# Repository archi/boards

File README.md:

A collection of board layouts, licensed under CC-BY-SA-NC 3.0 (commercial license available on request, see LICENSE file).

I am not an electronics engineer, so take these layouts with a grain of salt.

# opa1622-breakout/

A simple breakout board to fit VSON10 op amps (like the OPA1622) into a DIP-8 socket.
Pin 1 is rectangular, the others are round.
Please be aware, the OPA1622 has 2 additional pins:

1. GND, which also connects to the board GND plane and which should be connected to a clean GND.
   If you use a virtual GND, I can not say if that's good for you.
   The IC GND pin is routed to the via next to the DIP pin 1.
   
2. The ENable pin is used to turn the IC on/off by switching it to V+.
   It is routed to the via next to DIP pin 5.
   Per default, it is always connected with a bottom line to V+, going from the via to DIP pin 5.
   If you want to control it via an external signal, cut that line and connect the via to your controller.
   
The OPA1622 datasheet suggests adding two decoupling capacitors from V+ and V- to GND. If you want to add them, there are SMD pads for those (0805 in).
  
**This board is not yet tested!** I'll do a fab run once I have more boards for a panel, and publish a note here on how to get any spares (costs will be just those I had, but feel free to tip).

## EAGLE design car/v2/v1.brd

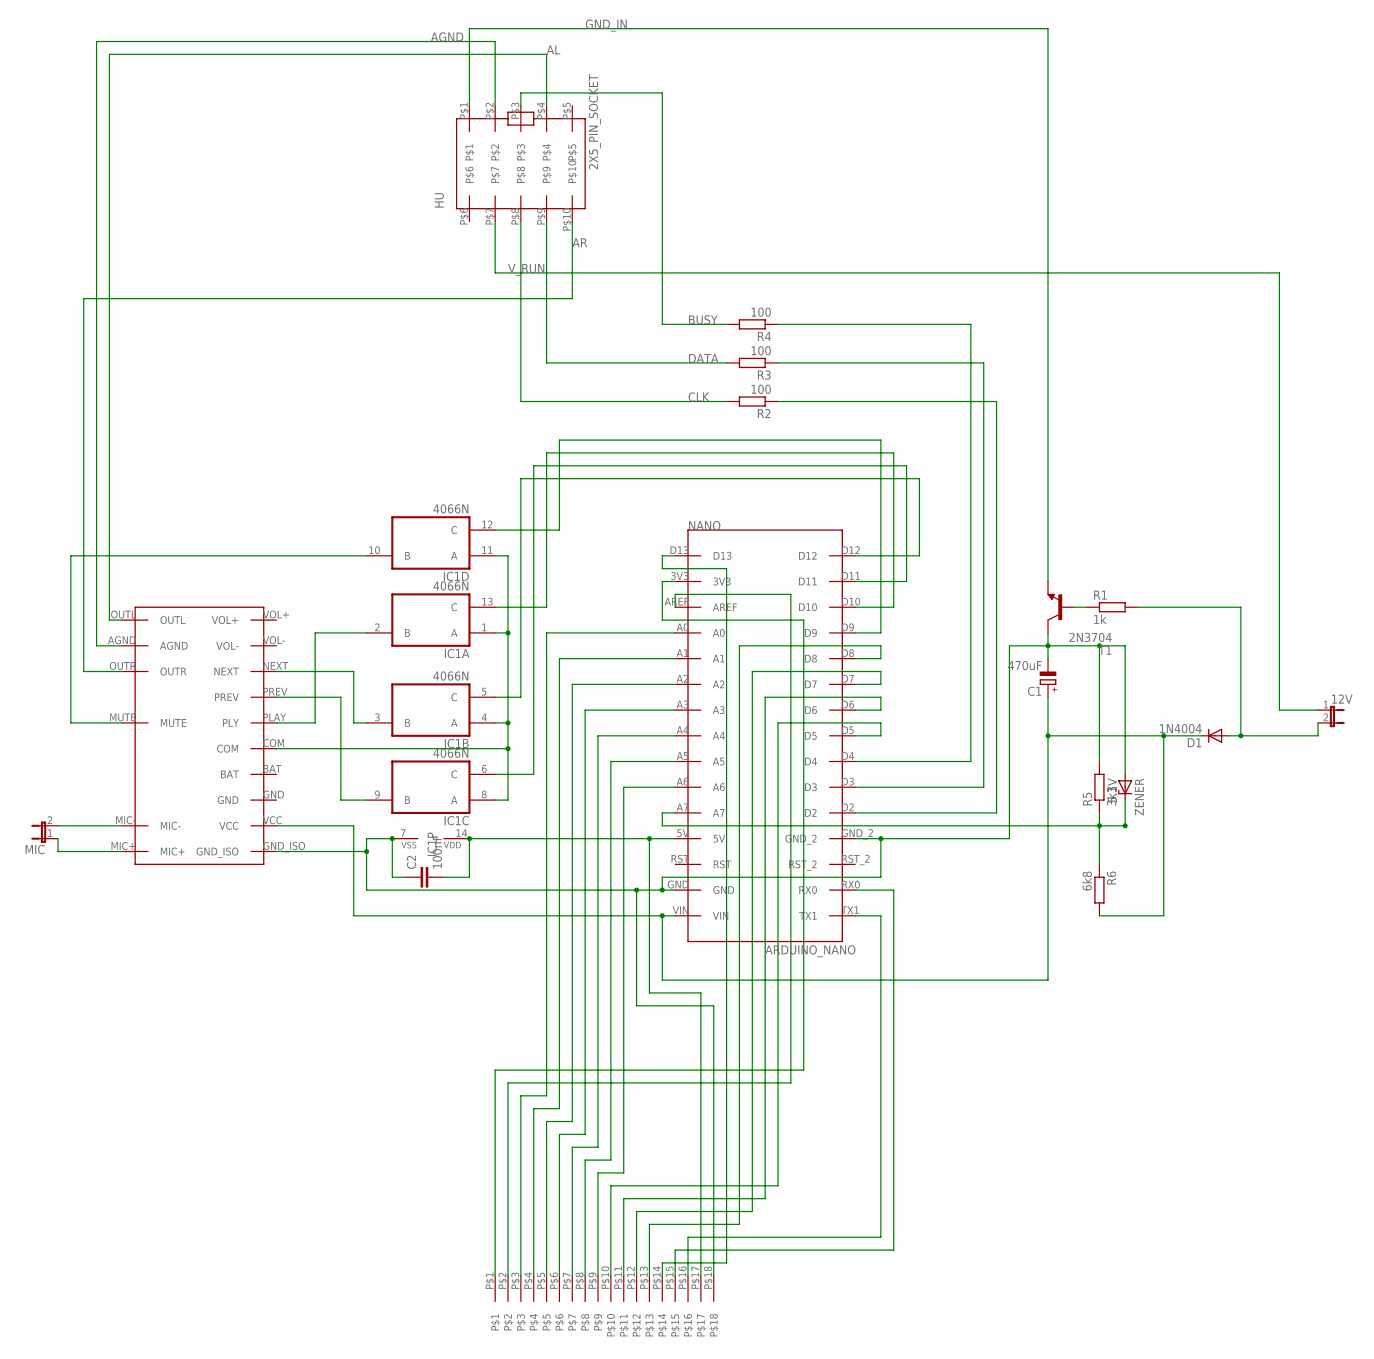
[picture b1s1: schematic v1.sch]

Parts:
12V: JP1E; JP1
C1: 470uF; E3,5-8
C2: 100nF; C1206
D1: 1N4004; DO41-10
HU: 2X5_PIN_SOCKET
IC1: 4066N; DIL14
MIC: JP1E; JP1
NANO: ARDUINO_NANO
R1: 1k; 0207/10
R2, R3, R4: 100; 0207/10
R5: 3k3; 0207/10
R6: 6k8; 0207/10
T1: 2N3704; TO92
U$1: JMP18X1
U$2: CSR8645_MODULE
ZENER: 5.1V; DO41Z10

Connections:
12V: 12V.2, D1.A, R1.2
AGND: HU.P$2, U$2.AGND
AL: HU.P$4, U$2.OUTL
AR: HU.P$10, U$2.OUTR
BUSY: HU.P$3, R4.2
CLK: HU.P$8, R2.2
DATA: HU.P$9, R3.2
GND: C1.-, C2.1, IC1.7 (VSS), NANO.GND, NANO.GND_2, R5.2, T1.2 (C), U$1.P$18, U$2.GND_ISO, ZENER.A
GND_IN: HU.P$1, T1.3 (E)
unnamed: IC1.5 (C), NANO.D12
unnamed: IC1.6 (C), NANO.D11
unnamed: IC1.13 (C), NANO.D10
unnamed: IC1.12 (C), NANO.D9
unnamed: NANO.TX1, U$1.P$16
unnamed: IC1.1 (A), IC1.4 (A), IC1.8 (A), IC1.11 (A), U$2.COM
unnamed: R1.1, T1.1 (B)
unnamed: NANO.A7, R5.1, R6.1, ZENER.C
unnamed: IC1.2 (B), U$2.PLAY (PLY)
unnamed: NANO.RX0, U$1.P$15
unnamed: IC1.9 (B), U$2.PREV
unnamed: IC1.3 (B), U$2.NEXT
unnamed: NANO.D2, R2.1
unnamed: C2.2, IC1.14 (VDD), NANO.5V, U$1.P$17
unnamed: IC1.10 (B), U$2.MUTE
unnamed: NANO.D3, R3.1
unnamed: NANO.D4, R4.1
unnamed: NANO.D13, U$1.P$14
unnamed: NANO.D8, U$1.P$13
unnamed: NANO.D7, U$1.P$12
unnamed: NANO.D6, U$1.P$11
unnamed: NANO.D5, U$1.P$10
unnamed: NANO.A6, U$1.P$9
unnamed: NANO.A5, U$1.P$8
unnamed: NANO.A4, U$1.P$7
unnamed: NANO.A3, U$1.P$6
unnamed: NANO.A2, U$1.P$5
unnamed: NANO.A1, U$1.P$4
unnamed: NANO.A0, U$1.P$3
unnamed: NANO.AREF, U$1.P$2
unnamed: NANO.3V3, U$1.P$1
unnamed: MIC.1, U$2.MIC+
unnamed: MIC.2, U$2.MIC-
VCC: C1.+, D1.C, NANO.VIN, R6.2, U$2.VCC
V_RUN: 12V.1, HU.P$7

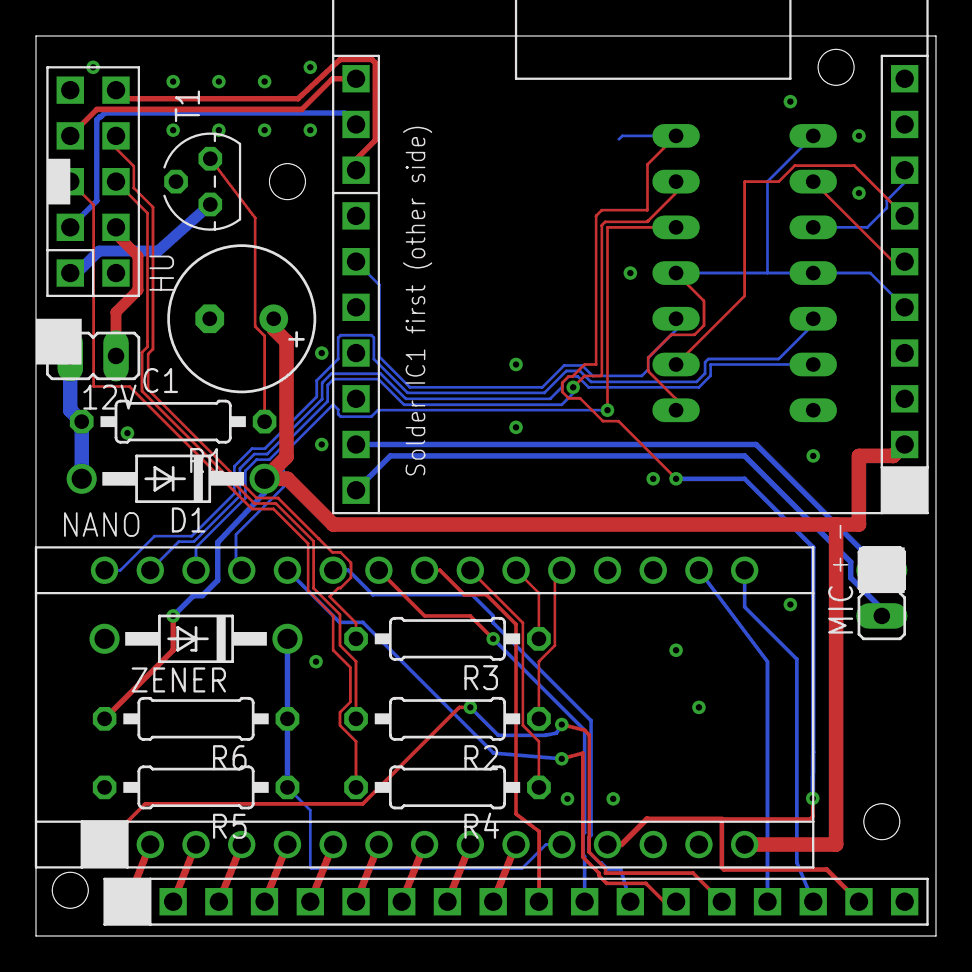
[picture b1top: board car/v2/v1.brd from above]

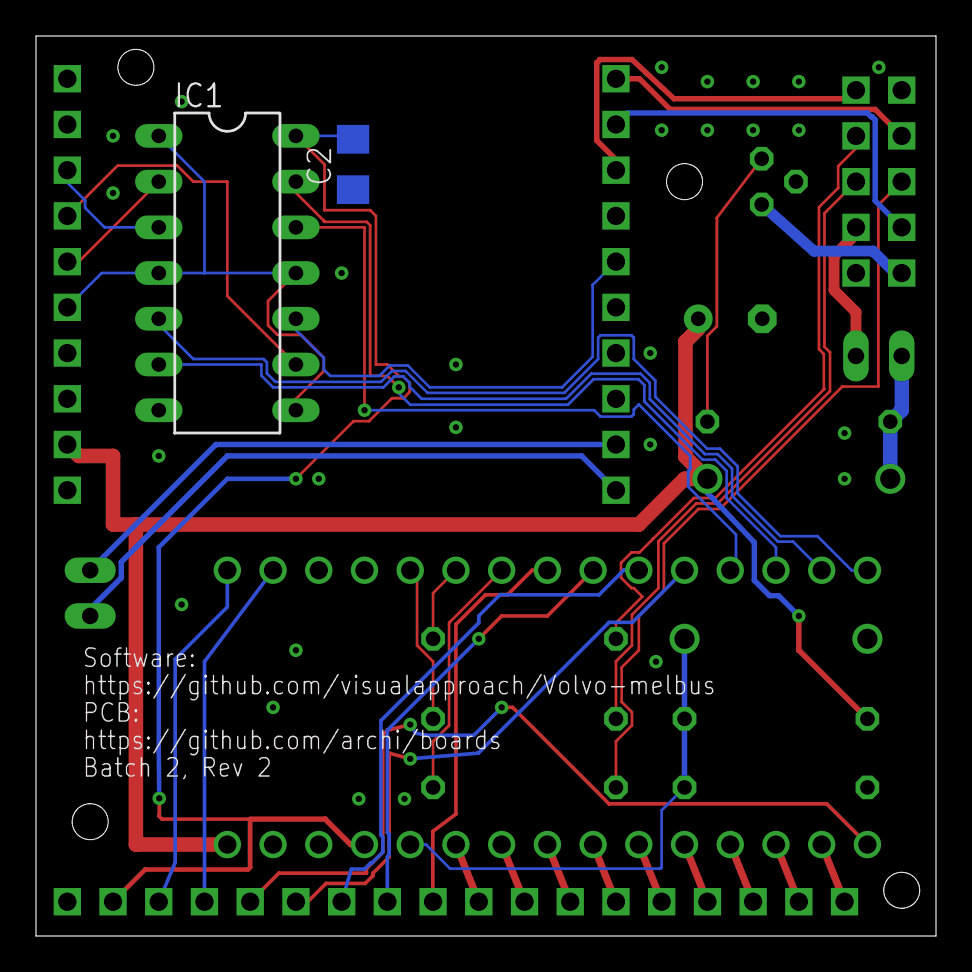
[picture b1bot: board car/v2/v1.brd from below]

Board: 2 copper layers, 50.0 x 50.0 mm, 18 parts (2 on the bottom side), 44 nets.

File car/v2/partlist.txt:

C2		100nF (on bottom!)
IC1		4066N (on bottom!)
C1		470uF
R1		1k
D1 		1N4004
R2,R3,R4	100R
ZENER		5.1V
R6		6k8
R5		3k3
HU		2x5 header
12V		1x2 header
NANO		Arduino Nano (USB port to the PCB edge)
BT		Bluetooth Module CSR8645 with 12V regulator (regulator "on top")

Careful with the 12V header, space is a bit tight to the HU header.

Pin Out HU Header
Numbering is non-default (sorry):
      ___
[1] 2 =3= 4  5
 6  7  8  9 10

PCB		MELBUS
 1 Gnd		Shield
 2 Audio Gnd	2
 3 Busy		5
 4 Audio Left	6
 5 NC		-
 6 NC		-
 7 V_Run (12V)	3 (optional)
 8 Clock	1
 9 Data		4
10 Audio Right	7

The 12V pin header:
The marked pin (outer pin) is connected to the Arduino Nano and the bluetooth module.
The unmarked inner pin is connected to V_Run.

Either connect the outer pin to an external 12V source (e.g. cigarette ligher), or connect the inner to the outer pin.

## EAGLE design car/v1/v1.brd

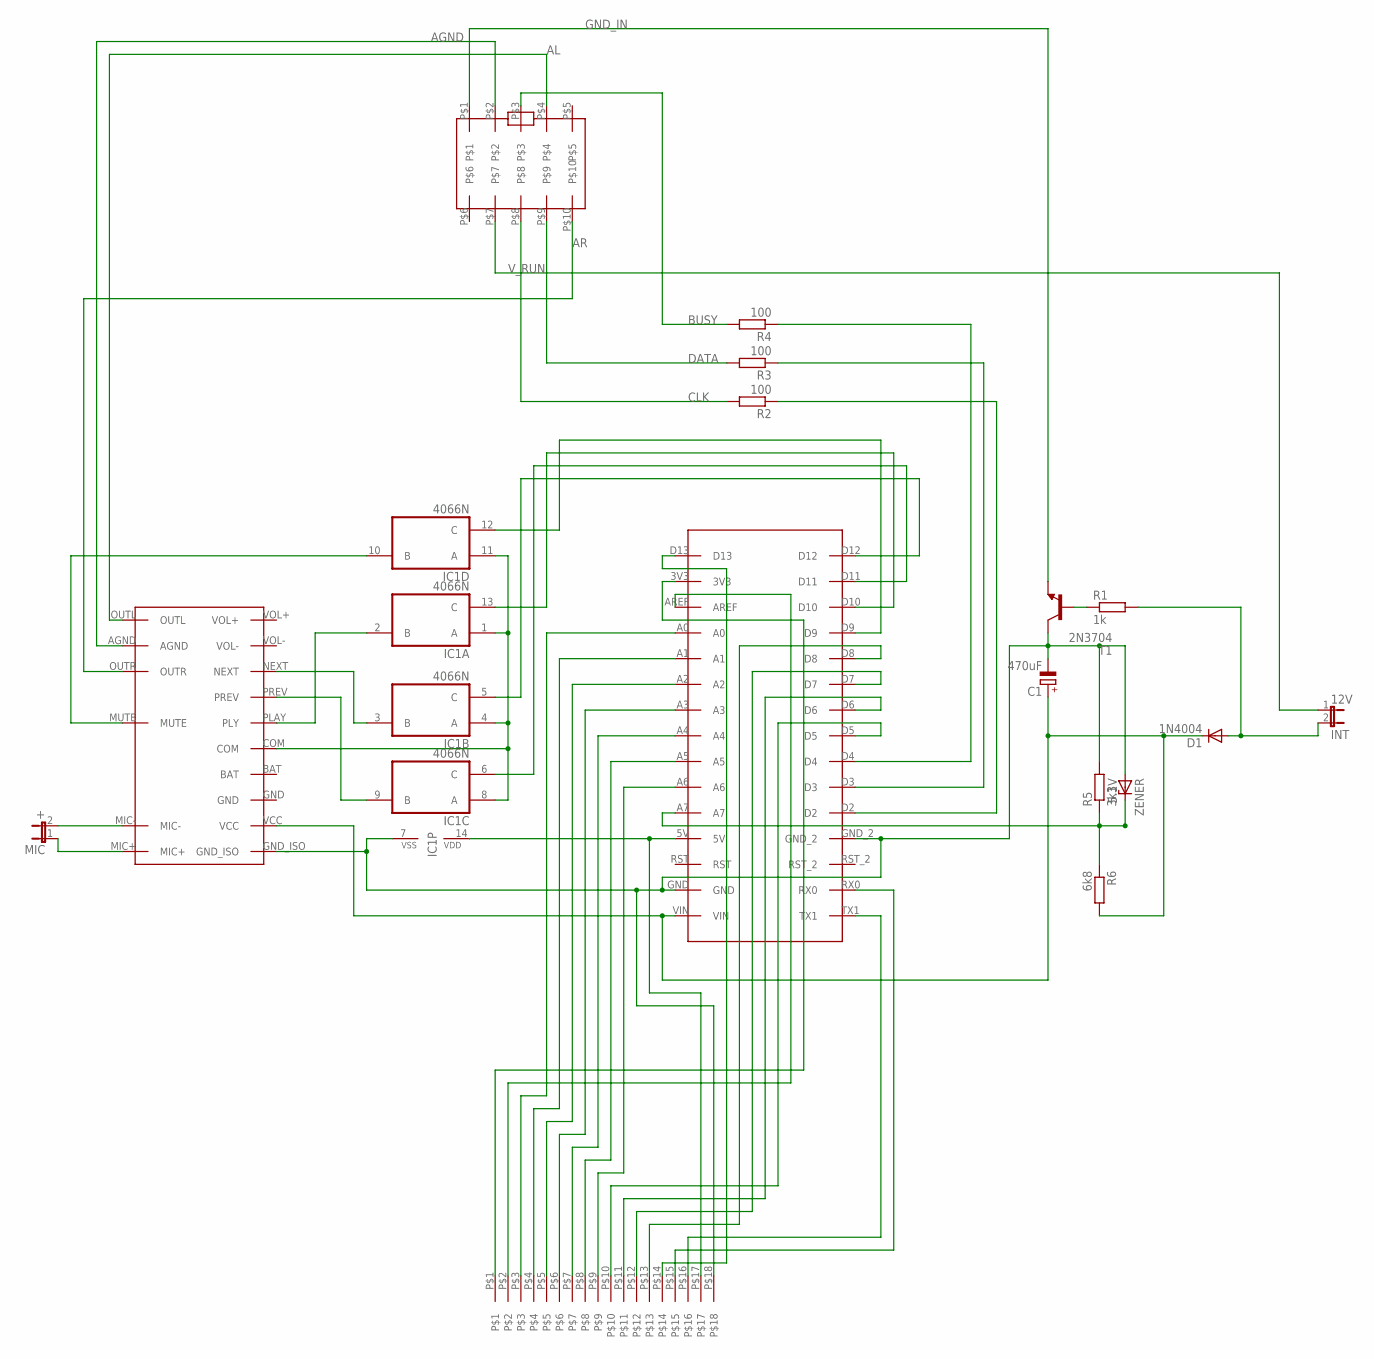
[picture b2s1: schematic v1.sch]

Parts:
12V: INT; JP1
C1: 470uF; E3,5-8
D1: 1N4004; DO41-10
IC1: 4066N; DIL14
MIC: +; JP1
R1: 1k; 0207/10
R2, R3, R4: 100; 0207/10
R5: 3k3; 0207/10
R6: 6k8; 0207/10
T1: 2N3704; TO92
U$1: JMP18X1
U$2: CSR8645_MODULE
U$4: 2X5_PIN_SOCKET
U$5: ARDUINO_NANO
ZENER: 5.1V; DO41Z10

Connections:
12V: 12V.2, D1.A, R1.2
AGND: U$2.AGND, U$4.P$2
AL: U$2.OUTL, U$4.P$4
AR: U$2.OUTR, U$4.P$10
BUSY: R4.2, U$4.P$3
CLK: R2.2, U$4.P$8
DATA: R3.2, U$4.P$9
GND: C1.-, IC1.7 (VSS), R5.2, T1.2 (C), U$1.P$18, U$2.GND_ISO, U$5.GND, U$5.GND_2, ZENER.A
GND_IN: T1.3 (E), U$4.P$1
unnamed: IC1.5 (C), U$5.D12
unnamed: IC1.6 (C), U$5.D11
unnamed: IC1.13 (C), U$5.D10
unnamed: IC1.12 (C), U$5.D9
unnamed: U$1.P$16, U$5.TX1
unnamed: IC1.1 (A), IC1.4 (A), IC1.8 (A), IC1.11 (A), U$2.COM
unnamed: R1.1, T1.1 (B)
unnamed: R5.1, R6.1, U$5.A7, ZENER.C
unnamed: IC1.2 (B), U$2.PLAY (PLY)
unnamed: U$1.P$15, U$5.RX0
unnamed: IC1.9 (B), U$2.PREV
unnamed: IC1.3 (B), U$2.NEXT
unnamed: R2.1, U$5.D2
unnamed: IC1.14 (VDD), U$1.P$17, U$5.5V
unnamed: IC1.10 (B), U$2.MUTE
unnamed: R3.1, U$5.D3
unnamed: R4.1, U$5.D4
unnamed: U$1.P$14, U$5.D13
unnamed: U$1.P$13, U$5.D8
unnamed: U$1.P$12, U$5.D7
unnamed: U$1.P$11, U$5.D6
unnamed: U$1.P$10, U$5.D5
unnamed: U$1.P$9, U$5.A6
unnamed: U$1.P$8, U$5.A5
unnamed: U$1.P$7, U$5.A4
unnamed: U$1.P$6, U$5.A3
unnamed: U$1.P$5, U$5.A2
unnamed: U$1.P$4, U$5.A1
unnamed: U$1.P$3, U$5.A0
unnamed: U$1.P$2, U$5.AREF
unnamed: U$1.P$1, U$5.3V3
unnamed: MIC.1, U$2.MIC+
unnamed: MIC.2, U$2.MIC-
VCC: C1.+, D1.C, R6.2, U$2.VCC, U$5.VIN
V_RUN: 12V.1, U$4.P$7

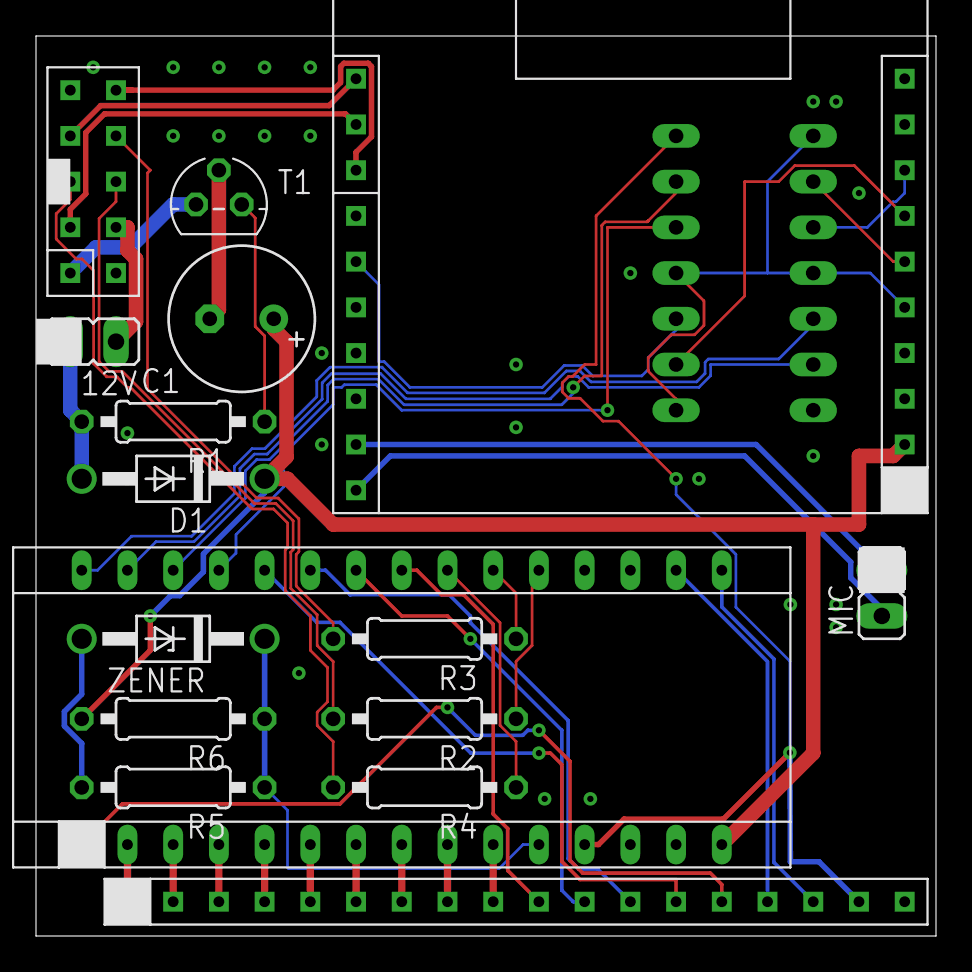
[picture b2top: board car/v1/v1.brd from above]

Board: 2 copper layers, 50.0 x 50.0 mm, 17 parts (1 on the bottom side), 44 nets.

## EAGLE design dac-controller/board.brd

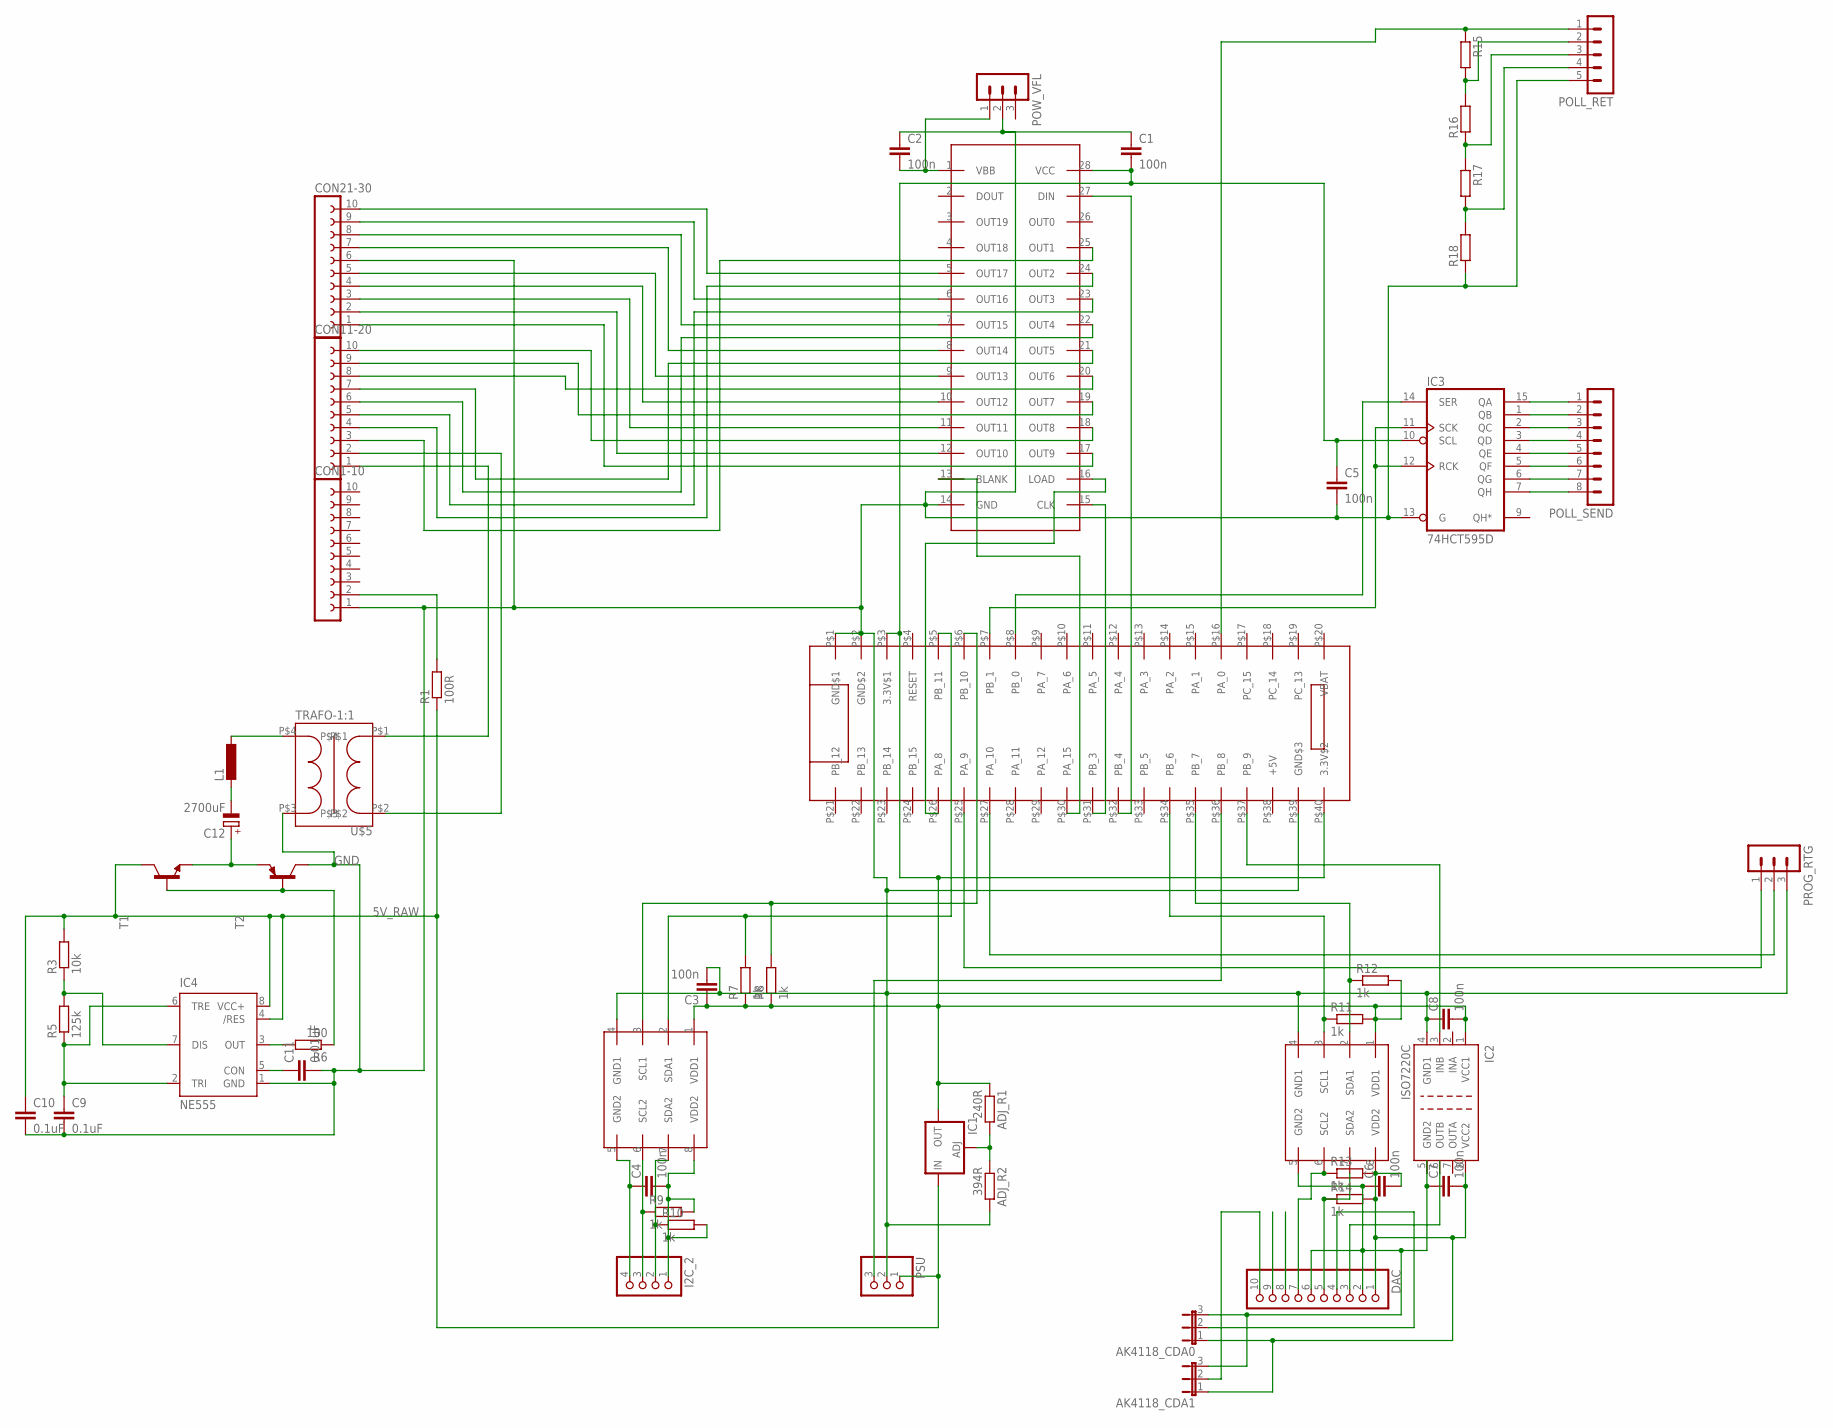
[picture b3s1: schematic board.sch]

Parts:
ADJ_R1: 240R; 0207/10
ADJ_R2: 394R; 0207/10
AK4118_CDA0, AK4118_CDA1: JP2E; JP2
C1, C2, C3, C4, C5, C6: 100n; C1206
C7, C8: 100n; C1210
C9, C10: 0.1uF; C1206
C11: 0.01uF; C1206
C12: 2700uF; E3,5-8
CON1-10, CON11-20, CON21-30: FE10-1; FE10
DAC: PINHD-1X10; 1X10
I2C_2: PINHD-1X4; 1X04
IC1: LM317TS; 317TS
IC2: ISO7220C; SO-08
IC3: 74HCT595D; SO16
IC4: NE555; DIL-08
L1: L-EU0204/5; 0204/5
POLL_RET: MA05-1
POLL_SEND: MA08-1
POW_VFL: MA03-1
PROG_RTG: MA03-1
PSU: PINHD-1X3; 1X03
R1: 100R; 0207/10
R3: 10k; R1206
R5: 125k; R1206
R6: 100; R1206
R7, R8, R9, R10, R11, R12, R13, R14: 1k; M1206
R15, R16, R17, R18: R-EU_M1206; M1206
T1: -NPN-TO92; TO92
T2: -PNP-TO92; TO92
U$1, U$2: ADUM1250; SO8
U$3: STM32F103C8T6_BOARD
U$4: MAX6921AWI; SO28L
U$5: TRAFO-1:1; TRAFO-10-12.5

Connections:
5V_RAW: C10.1, IC1.3 (IN), IC4.4 (/RES), IC4.8 (VCC+), PSU.1, R1.1, R3.2, T1.3 (C)
74HC_SELECT: DAC.3, IC2.6 (OUTB)
4118_CAD0: AK4118_CDA1.2, DAC.10
4118_CAD1: AK4118_CDA0.2, DAC.4
4490_CSN: DAC.9
4490_WCK: DAC.8
GND: ADJ_R2.2, C1.1, C2.1, C3.2, C5.2, C8.1, C9.2, C10.2, C11.2, CON1-10.1, CON21-30.6, IC2.4 (GND1), IC3.8 (GND), IC3.13 (G), IC4.1 (GND), POLL_RET.5, POW_VFL.2, PROG_RTG.3, PSU.2, R18.1, T2.3 (C), U$1.4 (GND1), U$2.4 (GND1), U$3.P$1 (GND$1), U$3.P$2 (GND$2), U$3.P$39 (GND$3), U$4.14 (GND), U$5.P$3
GND_DAC: AK4118_CDA0.3, AK4118_CDA1.3, C6.1, C7.1, DAC.2, DAC.6, IC2.5 (GND2), U$1.5 (GND2)
GND_I2C2: C4.1, I2C_2.4, U$2.5 (GND2)
I2C1_SDA: R12.1, U$1.2 (SDA1), U$3.P$35 (PB_7)
I2C1_SDL: R11.1, U$1.3 (SCL1), U$3.P$34 (PB_6)
I2C2_SDA: R7.2, U$2.2 (SDA1), U$3.P$5 (PB_11)
I2C2_SDL: R8.2, U$2.3 (SCL1), U$3.P$6 (PB_10)
unnamed: ADJ_R1.2, ADJ_R2.1, IC1.1 (ADJ)
unnamed: U$3.P$31 (PB_3), U$4.15 (CLK)
unnamed: IC3.11 (SCK), IC3.12 (RCK), U$3.P$7 (PB_1)
unnamed: I2C_2.3, R9.1, U$2.6 (SCL2)
unnamed: I2C_2.2, R10.1, U$2.7 (SDA2)
unnamed: C4.2, I2C_2.1, R9.2, R10.2, U$2.8 (VDD2)
unnamed: CON1-10.2, R1.2
unnamed: CON11-20.1, U$5.P$1
unnamed: CON11-20.2, U$5.P$2
unnamed: IC2.3 (INB), U$3.P$37 (PB_9)
unnamed: CON11-20.7, U$4.21 (OUT5)
unnamed: CON21-30.10, U$4.5 (OUT17)
unnamed: CON21-30.9, U$4.6 (OUT16)
unnamed: PROG_RTG.1, U$3.P$25 (PA_9)
unnamed: PROG_RTG.2, U$3.P$27 (PA_10)
unnamed: U$3.P$32 (PB_4), U$4.27 (DIN)
unnamed: U$3.P$26 (PA_8), U$4.16 (LOAD)
unnamed: U$3.P$30 (PA_15), U$4.13 (BLANK)
unnamed: CON21-30.8, U$4.7 (OUT15)
unnamed: CON21-30.7, U$4.8 (OUT14)
unnamed: CON21-30.5, U$4.9 (OUT13)
unnamed: CON21-30.4, U$4.10 (OUT12)
unnamed: CON21-30.3, U$4.11 (OUT11)
unnamed: C2.2, POW_VFL.1, U$4.1 (VBB)
unnamed: IC3.14 (SER), U$3.P$8 (PB_0)
unnamed: IC3.15 (QA), POLL_SEND.1
unnamed: IC3.1 (QB), POLL_SEND.2
unnamed: IC3.2 (QC), POLL_SEND.3
unnamed: IC3.3 (QD), POLL_SEND.4
unnamed: IC3.4 (QE), POLL_SEND.5
unnamed: CON21-30.2, U$4.12 (OUT10)
unnamed: CON21-30.1, U$4.17 (OUT9)
unnamed: CON11-20.10, U$4.18 (OUT8)
unnamed: CON11-20.9, U$4.19 (OUT7)
unnamed: CON11-20.8, U$4.20 (OUT6)
unnamed: CON11-20.6, U$4.22 (OUT4)
unnamed: CON11-20.5, U$4.23 (OUT3)
unnamed: CON11-20.4, U$4.24 (OUT2)
unnamed: CON11-20.3, U$4.25 (OUT1)
unnamed: C11.1, IC4.5 (CON)
unnamed: IC4.7 (DIS), R3.1, R5.2
unnamed: C9.1, IC4.2 (TRI), IC4.6 (TRE), R5.1
unnamed: IC4.3 (OUT), R6.2
unnamed: C12.+, T1.1 (E), T2.1 (E)
unnamed: L1.1, U$5.P$4
unnamed: IC3.5 (QF), POLL_SEND.6
unnamed: IC3.6 (QG), POLL_SEND.7
unnamed: IC3.7 (QH), POLL_SEND.8
unnamed: R6.1, T1.2 (B), T2.2 (B)
unnamed: POLL_RET.1, R15.1, U$3.P$16 (PA_0)
unnamed: POLL_RET.2, R15.2, R16.2
unnamed: POLL_RET.3, R16.1, R17.1
unnamed: POLL_RET.4, R17.2, R18.2
unnamed: C12.-, L1.2
RELAY_CTRL: PSU.3, U$3.P$36 (PB_8)
SCL: DAC.7, R13.1, U$1.6 (SCL2)
SDA: DAC.5, R14.1, U$1.7 (SDA2)
VCC: ADJ_R1.1, C1.2, C3.1, C5.1, C8.2, IC1.2 (OUT), IC2.1 (VCC1), IC3.10 (SCL), IC3.16 (VCC), R7.1, R8.1, R11.2, R12.2, U$1.1 (VDD1), U$2.1 (VDD1), U$3.P$3 (3.3V$1), U$3.P$40 (3.3V$2), U$4.28 (VCC)
VCC_DAC: AK4118_CDA0.1, AK4118_CDA1.1, C6.2, C7.2, DAC.1, IC2.8 (VCC2), R13.2, R14.2, U$1.8 (VDD2)

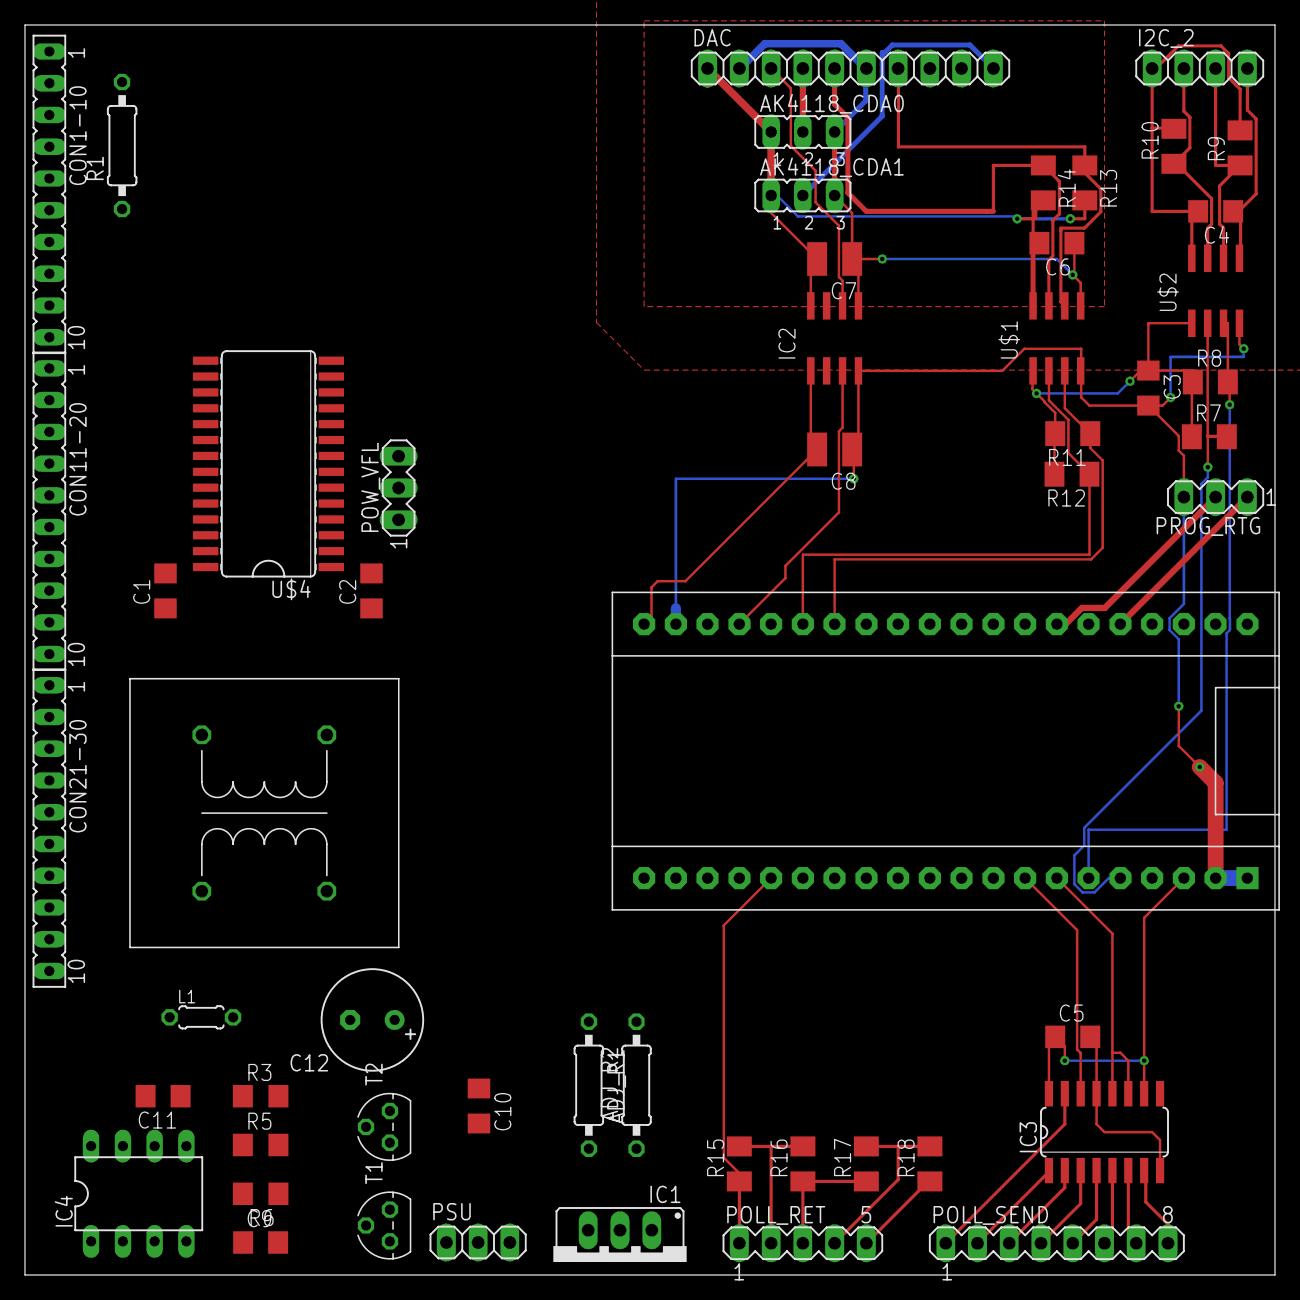
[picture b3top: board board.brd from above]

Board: 2 copper layers, 100.0 x 100.0 mm, 54 parts (0 on the bottom side), 70 nets.

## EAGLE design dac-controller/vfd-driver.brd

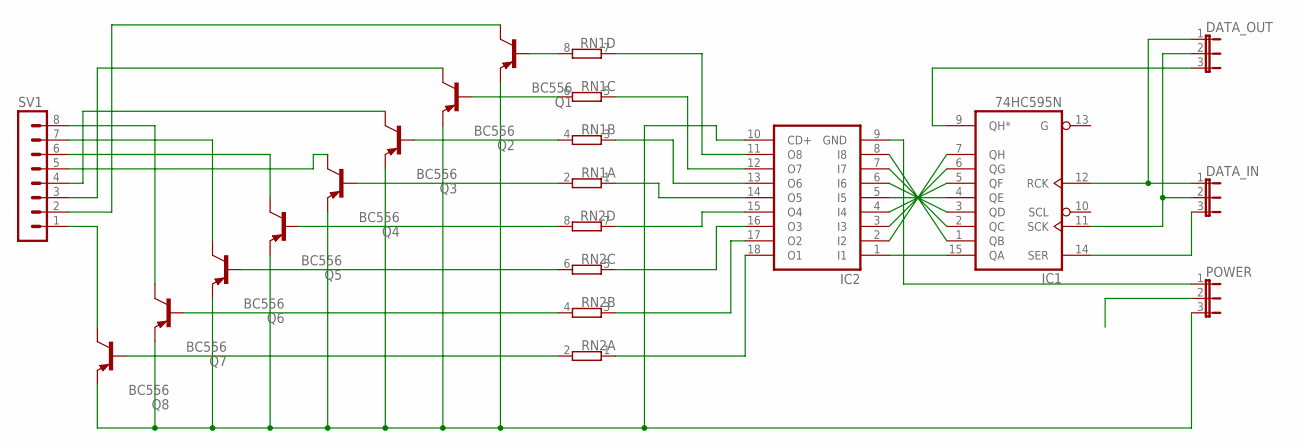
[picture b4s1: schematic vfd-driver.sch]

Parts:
DATA_IN: JP2E; JP2
DATA_OUT: JP2E; JP2
IC1: 74HC595N; DIL16
IC2: ULN2803A; DIL18
POWER: JP2E; JP2
Q1, Q2, Q3, Q4, Q5, Q6, Q7, Q8: BC556; TO92-EBC
RN1, RN2: E4R; SIL8
SV1: MA08-1

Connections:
DATA_IN: DATA_IN.3, IC1.14 (SER)
GND: IC1.8 (GND), IC2.9 (GND), POWER.1
unnamed: Q1.B, RN1.8 (2)
unnamed: Q2.B, RN1.6 (2)
unnamed: Q3.B, RN1.4 (2)
unnamed: Q4.B, RN1.2
unnamed: Q5.B, RN2.8 (2)
unnamed: Q6.B, RN2.6 (2)
unnamed: Q7.B, RN2.4 (2)
unnamed: Q8.B, RN2.2
unnamed: IC2.18 (O1), RN2.1
unnamed: IC2.17 (O2), RN2.3 (1)
unnamed: IC2.16 (O3), RN2.5 (1)
unnamed: IC2.15 (O4), RN2.7 (1)
unnamed: IC2.11 (O8), RN1.7 (1)
unnamed: IC2.12 (O7), RN1.5 (1)
unnamed: IC2.13 (O6), RN1.3 (1)
unnamed: IC2.14 (O5), RN1.1
unnamed: IC1.1 (QB), IC2.8 (I8)
unnamed: IC1.2 (QC), IC2.7 (I7)
unnamed: IC1.3 (QD), IC2.6 (I6)
unnamed: IC1.4 (QE), IC2.5 (I5)
unnamed: IC1.5 (QF), IC2.4 (I4)
unnamed: IC1.6 (QG), IC2.3 (I3)
unnamed: IC1.7 (QH), IC2.2 (I2)
unnamed: IC1.15 (QA), IC2.1 (I1)
unnamed: Q8.C, SV1.1
unnamed: Q7.C, SV1.8
unnamed: Q6.C, SV1.7
unnamed: Q5.C, SV1.6
unnamed: Q4.C, SV1.5
unnamed: Q3.C, SV1.4
unnamed: Q2.C, SV1.3
unnamed: Q1.C, SV1.2
unnamed: DATA_IN.2, DATA_OUT.2, IC1.11 (SCK)
unnamed: DATA_IN.1, DATA_OUT.1, IC1.12 (RCK)
unnamed: DATA_OUT.3, IC1.9 (QH*)
VCC: IC1.16 (VCC), POWER.2
VSS: IC2.10 (CD+), POWER.3, Q1.E, Q2.E, Q3.E, Q4.E, Q5.E, Q6.E, Q7.E, Q8.E

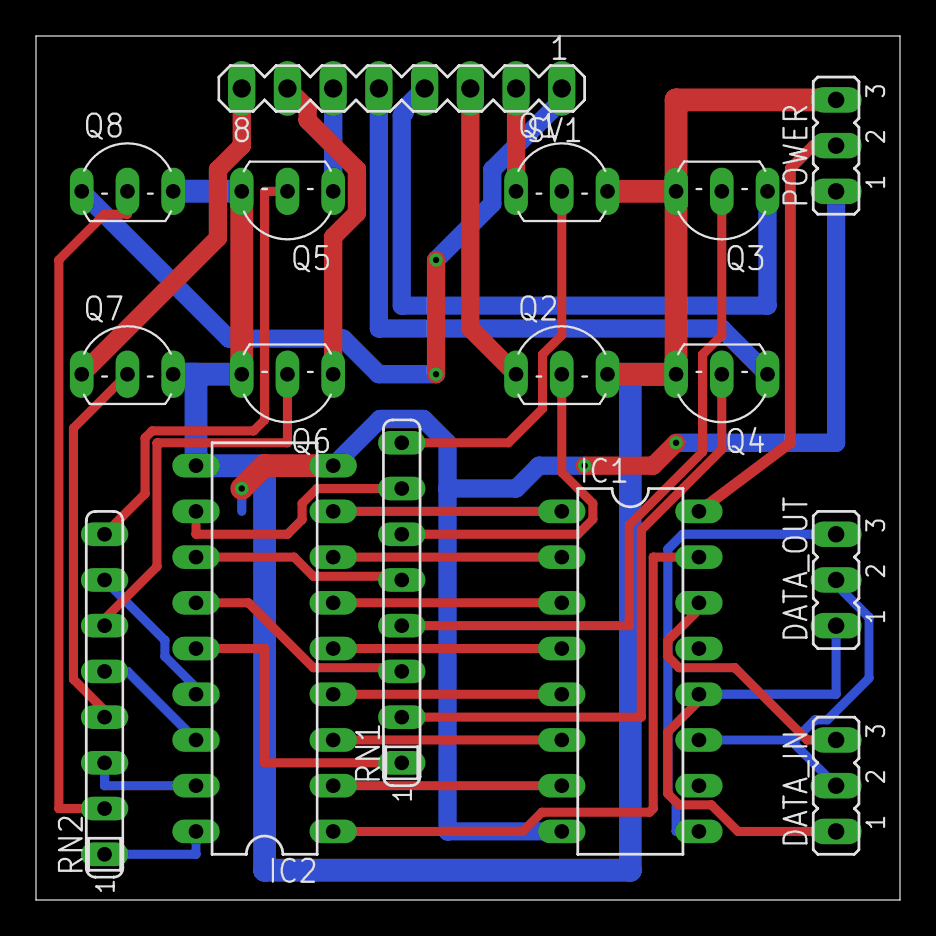
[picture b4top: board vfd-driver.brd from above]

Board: 2 copper layers, 48.0 x 48.0 mm, 16 parts (0 on the bottom side), 39 nets.

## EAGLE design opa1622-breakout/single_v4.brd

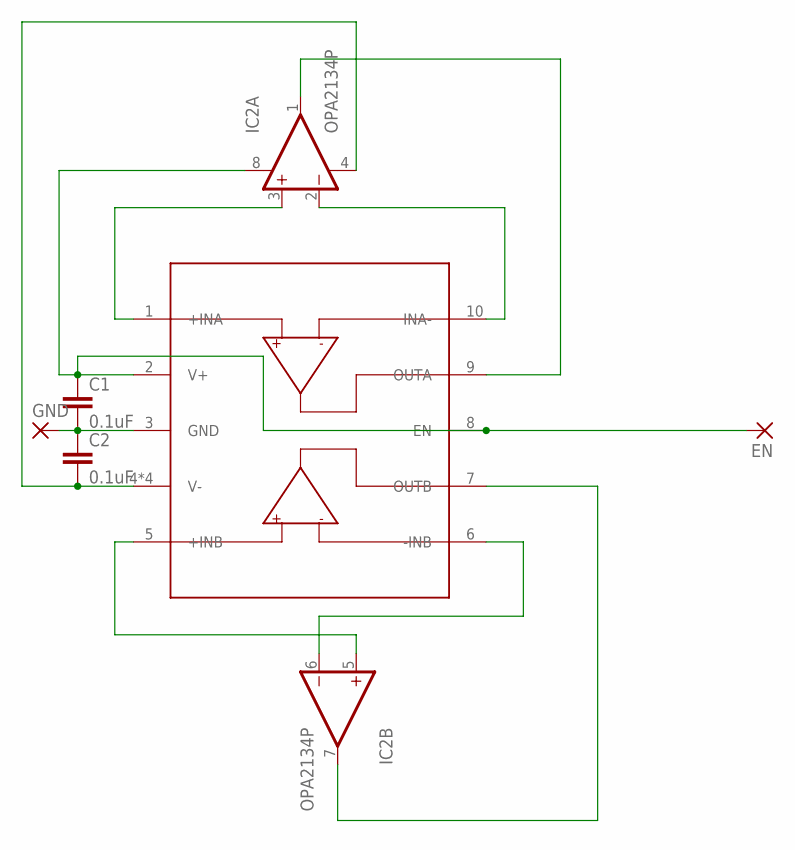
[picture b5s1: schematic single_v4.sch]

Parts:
C1, C2: 0.1uF; C0805
EN: 1,6/0,8
GND: 1,6/0,8
IC1: OPA1622; S-PDSO-N10
IC2: OPA2134P; DIL08

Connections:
+INA: IC1.1 (+INA), IC2.3 (+IN)
+INB: IC1.5 (+INB), IC2.5 (+IN)
-INA: IC1.10 (INA-), IC2.2 (-IN)
-INB: IC1.6 (-INB), IC2.6 (-IN)
GND: C1.2, C2.1, GND.1, IC1.3 (GND)
OUTA: IC1.9 (OUTA), IC2.1 (OUT)
OUTB: IC1.7 (OUTB), IC2.7 (OUT)
V+: C1.1, EN.1, IC1.2 (V+), IC1.8 (EN), IC2.8 (V+)
V-: C2.2, IC1.4 (V-), IC1.PP (V-), IC1.PP@1 (V-), IC1.PP@2 (V-), IC2.4 (V-)

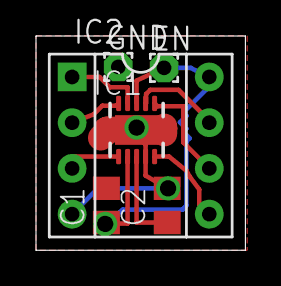
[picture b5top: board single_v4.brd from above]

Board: 2 copper layers, 11.6 x 11.9 mm, 6 parts (0 on the bottom side), 9 nets.

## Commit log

2017-04-14 initial commit of the opa1622 breakout
2017-04-14 Update README.md
    added a remark
2017-04-14 added my library of custom parts
2018-01-22 vfd driver [deprecated] and control board [in dev[
2018-01-22 added dc-ac convert, added correct connector(s) for VFD, ripped up some traces to move things around
2018-09-09 created a pcb for https://github.com/visualapproach/Volvo-melbus/issues/16
2018-09-09 comitted too much
2018-09-13 batch 1
2018-10-08 Added partlist and images
2018-10-08 remove v1
2018-11-20 updated board
